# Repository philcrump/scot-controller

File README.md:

# scot-controller

Antenna Motion Controller for the SCOT.

The board is an adaptor board that fits on the back of an [STM32F746NG Discovery Development Board](https://www.st.com/en/evaluation-tools/32f746gdiscovery.html).

* STM32F746NG Microcontroller
* 4.3” RGB 480×272 color LCD-TFT with capacitive touch screen
* 100Mb/s Ethernet Interface

The firmware for the board uses ChibiOS, uGFX, and lwIP.

## Adaptor Board Features

* 9-36V DC Input
* MCP2562 CAN 2.0A/B Communication Interface

[**Circuit Board Schematic**](https://github.com/philcrump/scot-controller/raw/master/scot-controller-schematic.pdf)

### Adaptor PCB (CAD Render)

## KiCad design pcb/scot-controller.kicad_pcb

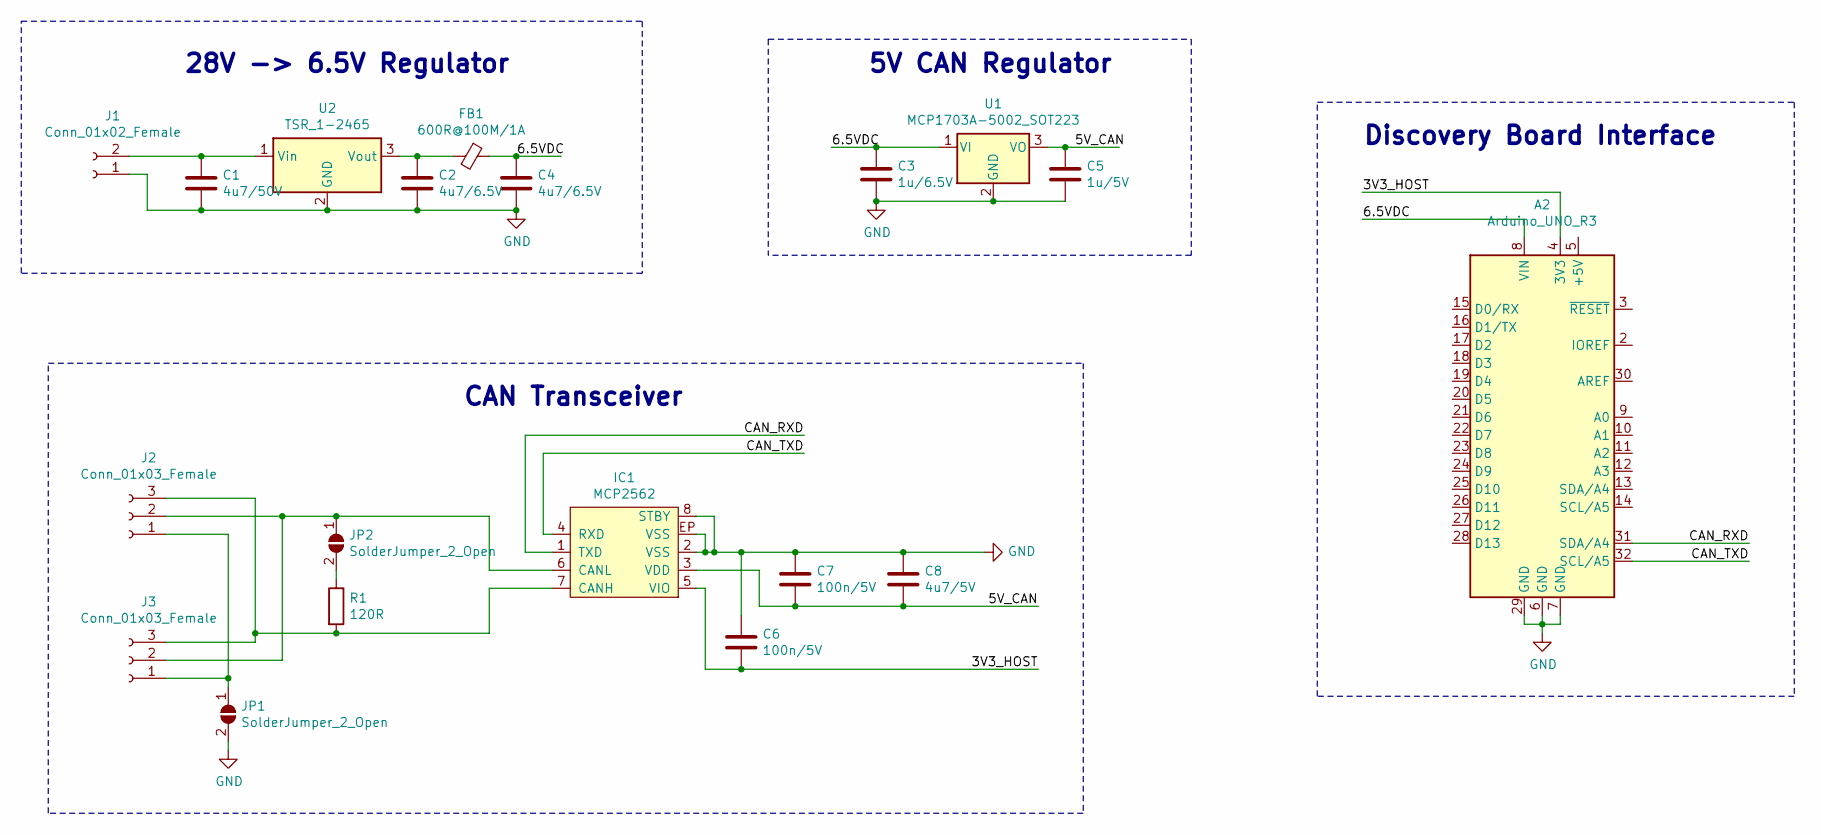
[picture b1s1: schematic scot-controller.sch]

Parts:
A2: Arduino_UNO_R3
C1: 4u7/50V; C_1206_3216Metric_Pad1.42x1.75mm_HandSolder
C2, C4: 4u7/6.5V; C_0805_2012Metric_Pad1.15x1.40mm_HandSolder
C3: 1u/6.5V; C_0603_1608Metric_Pad1.05x0.95mm_HandSolder
C5: 1u/5V; C_0603_1608Metric_Pad1.05x0.95mm_HandSolder
C6, C7: 100n/5V; C_0603_1608Metric_Pad1.05x0.95mm_HandSolder
C8: 4u7/5V; C_0805_2012Metric_Pad1.15x1.40mm_HandSolder
FB1: 600R@100M/1A; L_0805_2012Metric_Pad1.15x1.40mm_HandSolder
IC1: MCP2562; SOIC-8-EP
J1: Conn_01x02_Female; TerminalBlock_TE_282834-2_1x02_P2.54mm_Horizontal
J2, J3: Conn_01x03_Female; TerminalBlock_TE_282834-3_1x03_P2.54mm_Horizontal
JP1, JP2: SolderJumper_2_Open; SolderJumper-2_P1.3mm_Open_RoundedPad1.0x1.5mm
R1: 120R; R_0805_2012Metric_Pad1.15x1.40mm_HandSolder
U1: MCP1703A-5002_SOT223; SOT-223-3_TabPin2
U2: TSR_1-2465; Converter_DCDC_TRACO_TSR-1_THT

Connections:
/3V3_HOST: A2.4 (3V3), C6.2, IC1.5 (VIO)
/5V_CAN: C5.1, C7.2, C8.2, IC1.3 (VDD), U1.3 (VO)
/6.5VDC: A2.8 (VIN), C3.1, C4.1, FB1.1, U1.1 (VI)
/CAN_RXD: A2.31 (SDA/A4), IC1.1 (TXD)
/CAN_TXD: A2.32 (SCL/A5), IC1.4 (RXD)
GND: A2.6 (GND), A2.7 (GND), A2.29 (GND), C1.2, C2.2, C3.2, C4.2, C5.2, C6.1, C7.1, C8.1, IC1.2 (VSS), IC1.8 (STBY), IC1.EP (VSS), J1.1, JP1.2 (B), U1.2 (GND), U2.2 (GND)
unnamed: C1.1, J1.2, U2.1 (Vin)
unnamed: C2.1, FB1.2, U2.3 (Vout)
unnamed: IC1.6 (CANL), J2.2, J3.2, JP2.1 (A)
unnamed: IC1.7 (CANH), J2.3, J3.3, R1.2
unnamed: J2.1, J3.1, JP1.1 (A)
unnamed: JP2.2 (B), R1.1

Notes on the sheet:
CAN Transceiver
28V -> 6.5V Regulator
5V CAN Regulator
Discovery Board Interface

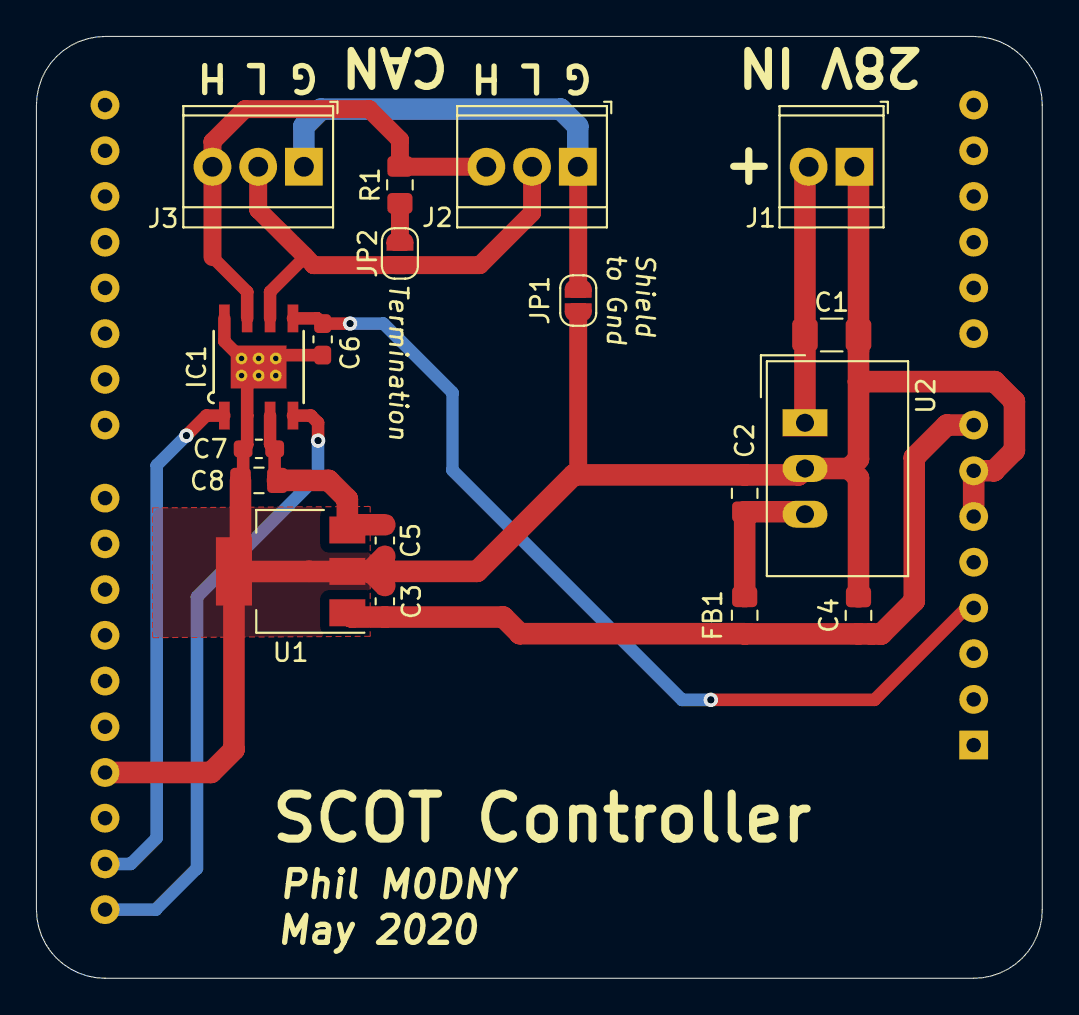
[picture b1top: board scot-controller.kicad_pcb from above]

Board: 2 copper layers, 55.9 x 52.3 mm, 19 parts (1 on the bottom side), 12 nets.

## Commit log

2020-04-08 Initial commit.
2020-04-08 Add CI config.
2020-04-19 Adaptor PCB for Power & CAN.
2020-04-19 pcb: Add BOM list. Adjust some values to reduce lines.
2020-04-26 firmware/ChibiOS: Update ref.
2020-04-26 firmware/uGFX: Update ref.
2020-04-26 firmware: Add WIP ugfx widget concepts.
2020-05-02 firmware/cfg/board.h: Fix ChibiOS bug 1092 (ARD_D5/D10 swapped mappings)
2020-05-02 firmware/ChibiOS: Update ref to latest 20.3.x
2020-05-02 firmware/build: Add multithread build option.
2020-05-02 Initial lwip.
2020-05-03 .travis.yml: Use multithread build in CI.
2020-05-03 firmware: Working CAN.
2020-05-03 datasheetts/: Add STM32F7 reference manual.
2020-05-03 firmware/: Minor CAN improvements, fix compile warning.
2020-05-20 README.md: Add Errata.
2020-05-23 firmware: Add UDP broadcast output & motor control input.
2020-05-23 firmware: Add lwIP as submodule, override ChibiOS bindings makefile for path. Fix CI.
2020-05-23 firmware: Tidy and fix warnings.
2020-05-23 lwIP: Update to latest 2.1.x head
2020-05-24 firmware: GFX improvements and structure tidy.
2020-05-27 firmware: IP progress (UDP M&C, NTP)
2020-05-27 pcb: Fix TXD/RXD mapping, move CAN regulator closer, add gitignore.
2020-05-28 pcb: Update schematic and CAD render.
2020-05-28 pcb: Remove outdated cam files.
2020-05-28 Update README.
2020-05-28 firmware: Large improvements, add watchdog.
2020-06-01 firmware/Chibi: Update ref.
2020-06-01 travis: Update to 2020 Q2 compiler.
2020-06-01 firmware/cfg/gfxconf: Disable GDispControl API to permit hardware rendering.
2020-06-09 firmware/Makefile: Enable GCC version check now Chibi bug #985 fixed.
2020-06-10 firmware/cfg/gfxconf.h: Enable more font sizes.
2020-06-10 firmware/: Screen progress.
2020-06-20 firmware/ChibiOS/: Update git ref.
2020-06-28 firmware: Remove ugfx bmps icons and modules.
2020-06-28 firmware: Add joystick control and switch enable.
2020-06-28 firmware/interface_udp.c: Improve pbuf handling in udp_rx.
2020-06-28 firmware/: Break out ip_link status functions.
2020-07-25 firmware/cfg/board.mk: Remove unused board.mk.
2020-07-25 firmware/cfg/chconf.h: Disable stack check.
2020-07-25 firmware/main.c: Remove unused math.h
2020-08-09 firmware/: Use structured CAN addresses.
2020-08-09 firmware/: Tweak UDP and joystick.
